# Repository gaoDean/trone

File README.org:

#+title:Trone

A 40 key keyboard similar to corne and ferris sweep.

gerber file is for jlcpcb

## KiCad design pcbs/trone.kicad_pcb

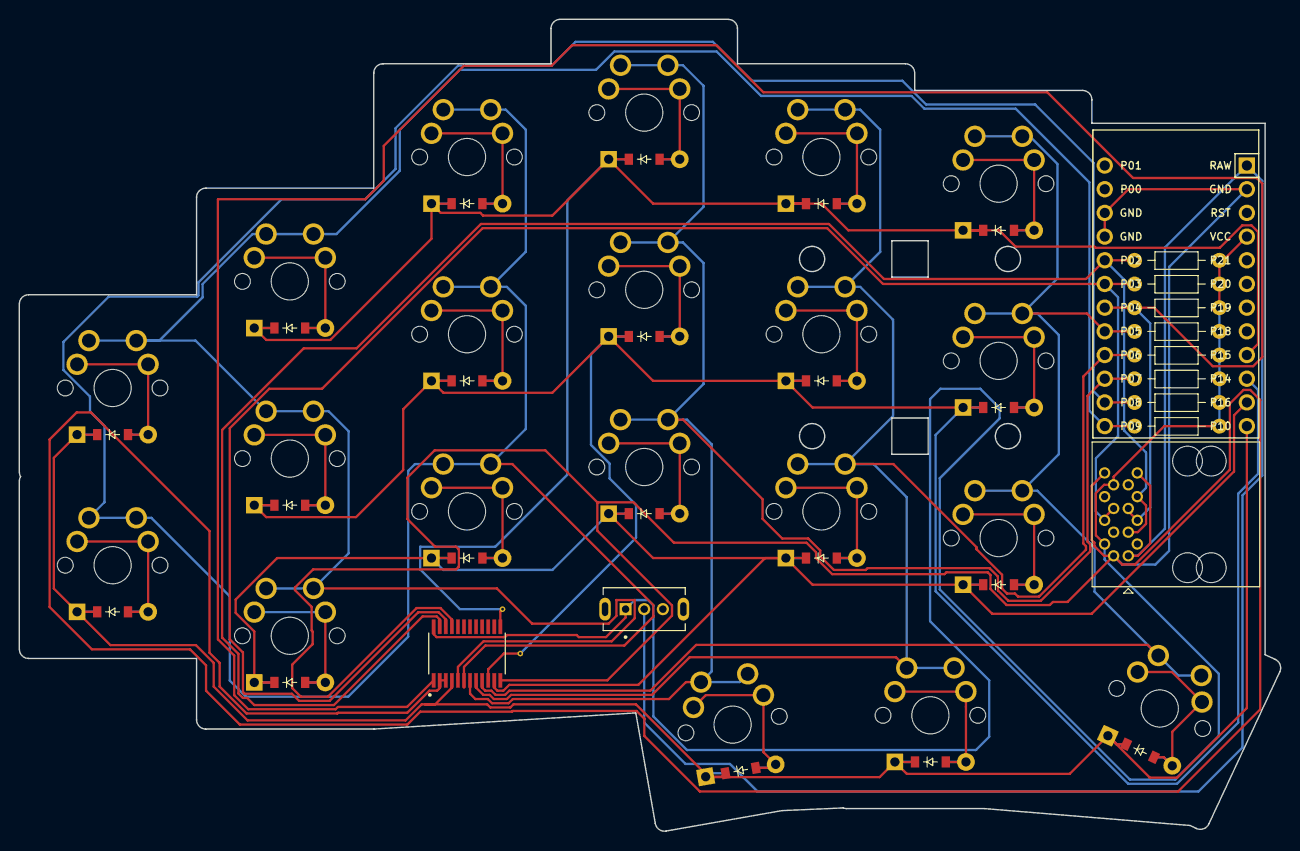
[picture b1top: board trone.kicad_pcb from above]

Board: 2 copper layers, 135.2 x 87.0 mm, 52 parts (0 on the bottom side), 35 nets.

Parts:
D1, D2, D3, D4, D5, D6, D7, D8, D9, D10, D11, D12, D13, D14, D15, D16, D17, D18, D19, D20: ComboDiode
EXP1: SOP65P640X120-24N
MCU1: ProMicro
R1, R2, R3, R4, R5, R6, R7, R8: Resistor
RJ451: RJ45_Amphenol_54602-x08_Horizontal
S1, S2, S3, S4, S5, S6, S7, S8, S9, S10, S11, S12, S13, S14, S15, S16, S17, S18, S19, S20: MX
SW1: SW_SS12D07VG4

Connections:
COL0: EXP1.9, MCU1.20, R5.2, S15.1, S16.1, S17.1, S20.1
COL1: EXP1.8, MCU1.21, R4.2, S12.1, S13.1, S14.1, S19.1
COL2: EXP1.7, MCU1.22, R3.2, S9.1, S10.1, S11.1, S18.1
COL3: EXP1.6, MCU1.23, R2.2, S1.1, S6.1, S7.1, S8.1
COL4: EXP1.5, MCU1.24, R1.2, S2.1, S3.1, S4.1, S5.1
GND: EXP1.2, EXP1.3, EXP1.12, EXP1.21, MCU1.2, MCU1.15, MCU1.16, RJ451.1, RJ451.8
INT: EXP1.1, MCU1.19, R6.2, RJ451.4, RJ451.5
RAW: MCU1.1, RJ451.1, RJ451.8, SW1.2
ROW0: D5.1, D8.1, D11.1, D14.1, D17.1, EXP1.13, MCU1.9
ROW1: D4.1, D7.1, D10.1, D13.1, D16.1, EXP1.10, MCU1.10
ROW2: D3.1, D6.1, D9.1, D12.1, D15.1, EXP1.11, MCU1.11
ROW3: D1.1, D2.1, D18.1, D19.1, D20.1, EXP1.4, MCU1.12
SCL: EXP1.22, MCU1.18, R7.2, RJ451.4, RJ451.5
SDA: EXP1.23, MCU1.17, R8.2, RJ451.3, RJ451.6
VCC: EXP1.24, MCU1.4, R1.1, R2.1, R3.1, R4.1, R5.1, R6.1, R7.1, R8.1, RJ451.2, RJ451.7, SW1.1
home_fan: D19.2, S19.2
index_bottom: D12.2, S12.2
index_home: D13.2, S13.2
index_top: D14.2, S14.2
inner_bottom: D15.2, S15.2
inner_fan: D18.2, S18.2
inner_home: D16.2, S16.2
inner_top: D17.2, S17.2
middle_bottom: D9.2, S9.2
middle_home: D10.2, S10.2
middle_top: D11.2, S11.2
outer_fan: D20.2, S20.2
outer_home: D1.2, S1.2
outer_top: D2.2, S2.2
pinky_bottom: D3.2, S3.2
pinky_home: D4.2, S4.2
pinky_top: D5.2, S5.2
ring_bottom: D6.2, S6.2
ring_home: D7.2, S7.2
ring_top: D8.2, S8.2

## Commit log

2023-06-04 init
2023-06-05 done
2023-06-05 fully routed
2023-06-05 gerber
2023-06-05 readme
2023-06-06 new pcb
